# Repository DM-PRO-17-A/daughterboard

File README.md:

# daughterboard
PCB for the PYNQ daughterboard

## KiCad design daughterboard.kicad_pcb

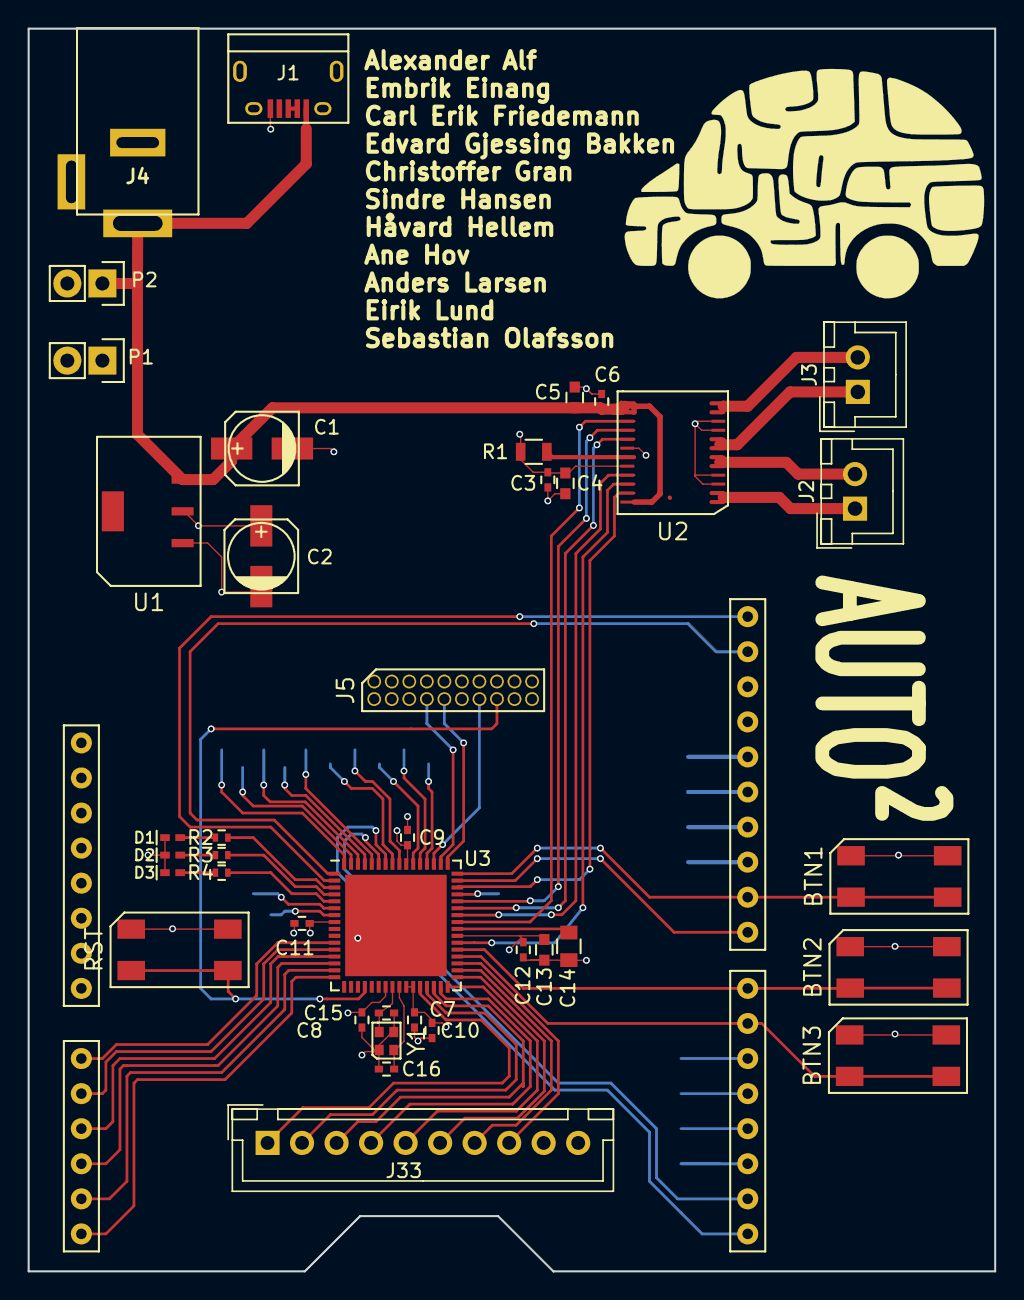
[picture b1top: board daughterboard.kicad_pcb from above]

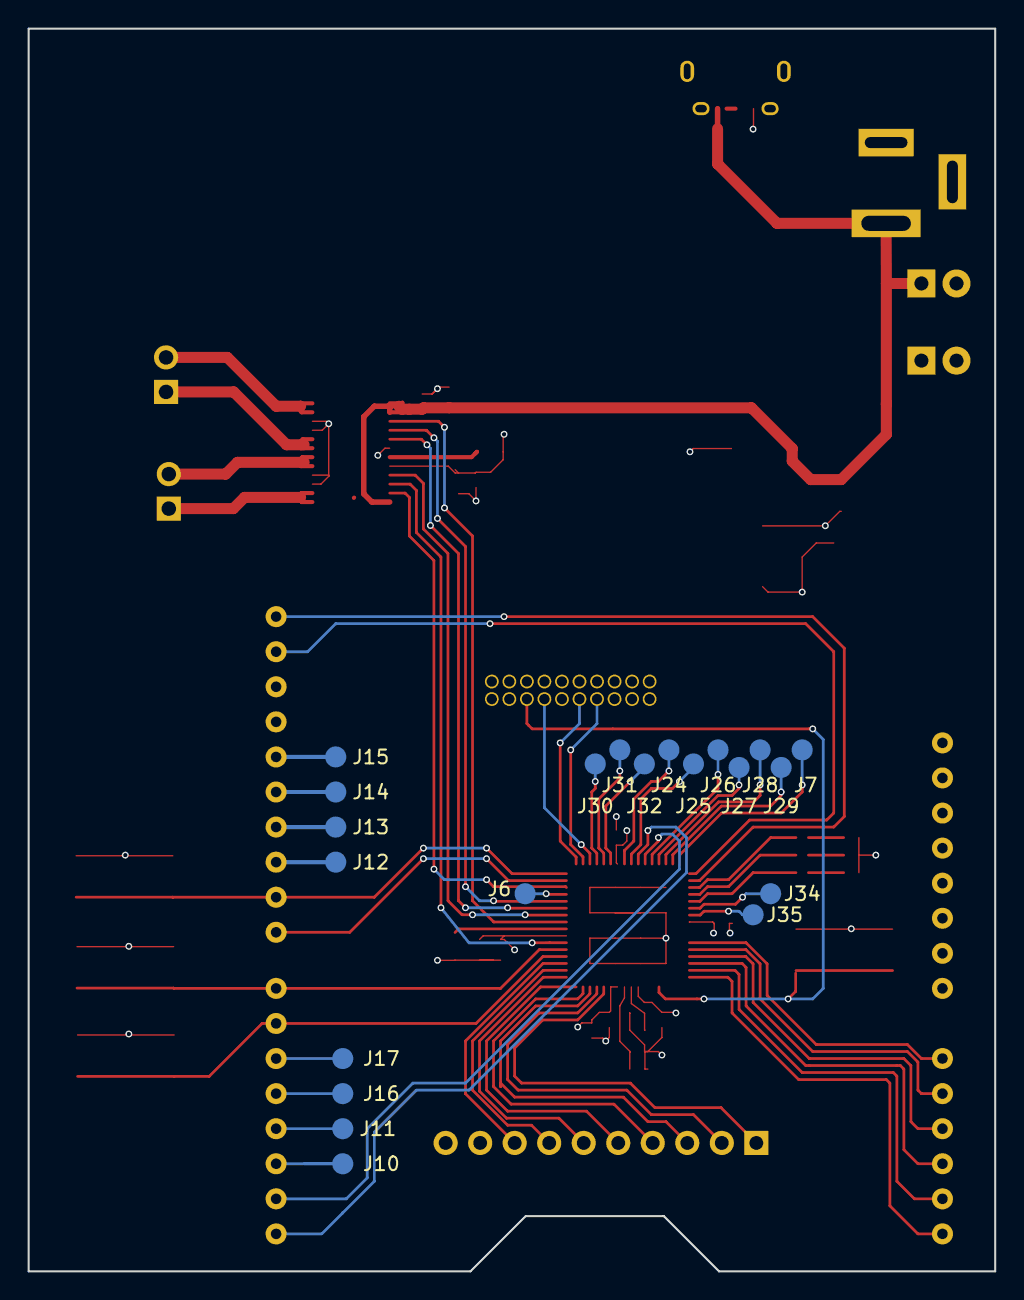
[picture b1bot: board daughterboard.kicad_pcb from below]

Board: 4 copper layers, 70.0 x 90.0 mm, 61 parts (21 on the bottom side), 71 nets.

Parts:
BTN1, BTN2, BTN3: Button; WS-TASV
C1, C2: 47uF; c_elec_5x5.3
C3, C6, C7, C8, C9, C10, C11, C12: 100nF; C_0402
C4, C5, C13: 10uF; C_0603
C14: 1uF; C_0805
C15, C16: 10pF; C_0402
D1, D2, D3: LED; LED-0402
J1: USB_OTG; USB_Micro-B
J2: MotorA; JST_XH_B02B-XH-A_02x2.50mm_Straight
J3: MotorB; JST_XH_B02B-XH-A_02x2.50mm_Straight
J4: BARREL_JACK; Barrel
J5: Debug; SOIC-20
J6, J7, J10, J11, J12, J13, J14, J15, J16, J17, J24, J25, J26, J27, J28, J29, J30, J31, J32, J34, J35: J; Measurement_Point_Round-SMD-Pad_Small
J33: QTR-8A; JST_XH_B10B-XH-A_10x2.50mm_Straight
P1, P2: CONN_01X02; Pin_Header_Straight_1x02
R1: 10k; R_0805
R2, R3, R4: R; R_0402
RST: Reset; WS-TASV
SHIELD1: ARDUINO_SHIELD; UNO_SHIELD
U1: LD1117S33CTR; SOT-223
U2: TB6612FNG; SOIC-24
U3: EFM32G230F128; QFN-64-1EP_9x9mm_Pitch0.5mm
Y1: Crystal; ABM11

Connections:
+3V3: BTN1.1, BTN1.2, BTN2.1, BTN2.2, BTN3.1, BTN3.2, C2.1, C3.1, C4.1, C7.1, C8.1, C9.1, C10.1, C11.1, C12.1, C13.1, J5.2, J33.9, P1.1, R1.2, U1.2, U2.20, U3.8, U3.23, U3.26, U3.27, U3.39, U3.55
+5V: C1.1, C5.1, C6.1, J1.1, J4.1, P2.1, U1.3, U2.13, U2.14, U2.24
/EFM32/ADC0_CH0: J33.1, U3.28
/EFM32/ADC0_CH1: J33.2, U3.29
/EFM32/ADC0_CH2: J33.3, U3.30
/EFM32/ADC0_CH3: J33.4, U3.31
/EFM32/ADC0_CH4: J33.5, U3.32
/EFM32/ADC0_CH5: J33.6, U3.33
/EFM32/ADC0_CH6: J33.7, U3.34
/EFM32/ADC0_CH7: J33.8, U3.35
/EFM32/AIN1: U2.21, U3.42
/EFM32/AIN2: U2.22, U3.38
/EFM32/BIN1: U2.17, U3.43
/EFM32/BIN2: U2.16, U3.44
/EFM32/DCPL: C14.1, U3.40
/EFM32/PA2: R2.1, U3.3
/EFM32/PA3: R3.1, U3.4
/EFM32/PA4: R4.1, U3.5
/EFM32/PA5: J34.1, U3.6
/EFM32/PA6: J35.1, U3.7
/EFM32/PA15: J7.1, U3.64
/EFM32/PB7: SHIELD1.A4, U3.15
/EFM32/PB8: SHIELD1.A5, U3.16
/EFM32/PB13: C15.1, U3.24, Y1.1
/EFM32/PB14: C16.1, U3.25, Y1.3
/EFM32/PC2: SHIELD1.A0, U3.11
/EFM32/PC3: SHIELD1.A1, U3.12
/EFM32/PC4: SHIELD1.A2, U3.13
/EFM32/PC5: SHIELD1.A3, U3.14
/EFM32/PC6: BTN2.3, BTN2.4, SHIELD1.7, U3.37
/EFM32/PC12: J6.1, U3.45
/EFM32/PC14: SHIELD1.8, U3.47
/EFM32/PC15: BTN1.3, BTN1.4, SHIELD1.9, U3.48
/EFM32/PD8: BTN3.3, BTN3.4, SHIELD1.6, U3.36
/EFM32/PE8: J24.1, U3.56
/EFM32/PE9: J25.1, U3.57
/EFM32/PE12: J26.1, U3.60
/EFM32/PE13: J27.1, U3.61
/EFM32/PE14: J28.1, U3.62
/EFM32/PE15: J29.1, U3.63
/EFM32/PF0: J5.9, U3.49
/EFM32/PF1: J5.7, U3.50
/EFM32/PF2: J5.13, U3.51
/EFM32/PF3: J30.1, U3.52
/EFM32/PF4: J31.1, U3.53
/EFM32/PF5: J32.1, U3.54
/EFM32/PWMA: U2.23, U3.46
/EFM32/PWMB: U2.15, U3.41
/EFM32/RESETn: J5.15, RST.3, RST.4, U3.20
/EFM32/RX: SHIELD1.1, U3.59
/EFM32/SCL: SHIELD1.SCL, U3.2
/EFM32/SDA: SHIELD1.SDA, U3.1
/EFM32/TX: SHIELD1.0, U3.58
/TB6612/MotorA1: J2.1, U2.1, U2.2
/TB6612/MotorA2: J2.2, U2.5, U2.6
/TB6612/MotorB1: J3.2, U2.11, U2.12
/TB6612/MotorB2: J3.1, U2.7, U2.8
/TB6612/STBY: R1.1, U2.19
GND: C1.2, C2.2, C3.2, C4.2, C5.2, C6.2, C7.2, C8.2, C9.2, C10.2, C11.2, C12.2, C13.2, C14.2, C15.2, C16.2, D1.1, D2.1, D3.1, J1.5, J1.6, J4.2, J4.3, J5.4, J5.6, J5.8, J5.10, J5.12, J5.14, J5.16, J5.18, J5.20, J33.10, P1.2, P2.2, RST.1, RST.2, SHIELD1.GND1, SHIELD1.GND2, SHIELD1.GND3, U1.1, U2.3, U2.4, U2.9, U2.10, U2.18, U3.65, Y1.2, Y1.4
unnamed: D1.2, R2.2
unnamed: D2.2, R3.2
unnamed: D3.2, R4.2
unnamed: J1.2, J1.3
unnamed: J10.1, SHIELD1.2
unnamed: J11.1, SHIELD1.3
unnamed: J12.1, SHIELD1.10
unnamed: J13.1, SHIELD1.11
unnamed: J14.1, SHIELD1.12
unnamed: J15.1, SHIELD1.13
unnamed: J16.1, SHIELD1.4
unnamed: J17.1, SHIELD1.5

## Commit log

2017-09-26 Add empty kicad project
2017-09-26 Ignore backup files
2017-09-26 Add efm32 library
2017-09-26 Added folder with datasheets
2017-09-27 Add TB6612 library
2017-09-27 Create hierarchical sheets
2017-09-27 Add hardware design doc
2017-09-27 add footprints: switch, TB6612, LD1117
2017-09-27 Add shield schematic
2017-09-27 Connect shield
    Most of the pins on the shield are connected.Some of the pins on
    the EFM32 still needs to be brought out to pads.
2017-09-30 Bring the rest of the EFM32 pins to pads
2017-09-30 add barrel jack footprint draft
2017-09-30 add barrel jack footprints oval holes
2017-09-30 add debugger footprints
2017-09-30 add EFM32 footprint
2017-10-01 Annotate schematic
2017-10-01 Add footprints for JST and Arduino
2017-10-01 Connect footprints to parts
2017-10-01 Add rough layout of pcb
2017-10-04 Add footprint for barrel jack
2017-10-04 Add usb micro to 5V bus and 3xled
2017-10-04 update footprint pin numbers and measures
2017-10-04 add fp-lib-table
2017-10-06 Add buttons, change the leds to be connected directly
2017-10-07 Add buttons, connected SDA and SCL and connect led directly
2017-10-07 add crystal footprint
2017-10-07 update barreljack pad numbers
2017-10-07 Remove buses and change the UART pins
2017-10-07 Add SCL and SDA pins to shield part
2017-10-07 Remove barrel jack drafts
2017-10-07 Add crystal to efm32
2017-10-07 add footprint for 4.5x4.5 button
2017-10-09 Update shield schematic and footprint
    - Fixed a naming error with the analog pins
    - Added SCL and SDA
2017-10-09 Update PCB to reflect schematic changes
    Since we reannotated just about the entire schematic it was easier
    to just clear the entire pcb and layout the components again.
    Moved the QR8 to the bottom and TB6612 to the top, since it made
    more sense wrt the pinout of the EFM32.
2017-10-09 Reannotate and add labels
    Since we moved away from buses it was easier to just reannotate
    the whole schematic.
    Also added labels to (nearly) every net, this makes the PCB far
    more readable.
2017-10-09 Fix merge conflicts
    Trying to merge manually with Kicad is a bad idea.
2017-10-09 Use round measurement pads
2017-10-09 Add schematic symbol for crystal
    Also some more of the square-to-round-pads stuff
2017-10-09 Use new, smaller components
2017-10-10 Route connection QTR-8A
2017-10-10 Route TB6612
2017-10-10 Create and use footprint for new, smaller switches
2017-10-10 Add routing of pads etc
    Nearly finished, just _one_ capacitor remaining
2017-10-10 Finish routing
    Could do with some cleanup, but it passes CRC.
2017-10-10 fix measurements on LD1117 footprint
2017-10-10 Add logo
    Also update footprint for barrel jack
2017-10-10 update TB6612 footprint
2017-10-10 Use new footprint for TB6612
2017-10-10 add footprint button
2017-10-10 Use new switch footprint
2017-10-11 update crystal footprint
2017-10-11 add gerbers
2017-10-11 update LD1117 footprint
2017-10-11 update gerbers
2017-10-13 Increase pad clearance around C11
2017-10-13 Update gerbers
    Included the 3V3-layer and the GND layer. Also generated a drill
    file.
2017-10-17 update soic-20 footprint
2017-10-18 Change via size
    Seems to be a problem with thermal relief on the vias
2017-10-18 Add names to Silkscreen
    Also updated gerbers with the new silk screen
2017-10-19 update uno sheild footprint
2017-11-07 add uart project
2017-11-07 remove uart project
